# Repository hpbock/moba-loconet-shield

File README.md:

# LocoNet Shield (February 2026 Version)

Copyright (c) 2026 Dr.-Ing. Hans-Peter Bock <ln-shield@avaapgh.de>

# License & Legal Notices

This hardware design (schematic and board layout) is a modified version (derivative work) of the "LocoShield" project by John Plocher (SPCoast Electronics).

Based on the conditions of the original license, this derivative work is licensed under the CERN Open Hardware Licence v1.2 (CERN OHL v1.2).

- The unmodified original schematic originates from the repository: <https://github.com/plocher/LocoShield>
- The full license text of the CERN OHL v1.2 is included in the [LICENSE.txt](LICENSE.txt) file within this repository.
- The source files for this modified design are permanently available at: <https://github.com/hpbock/moba-loconet-shield>

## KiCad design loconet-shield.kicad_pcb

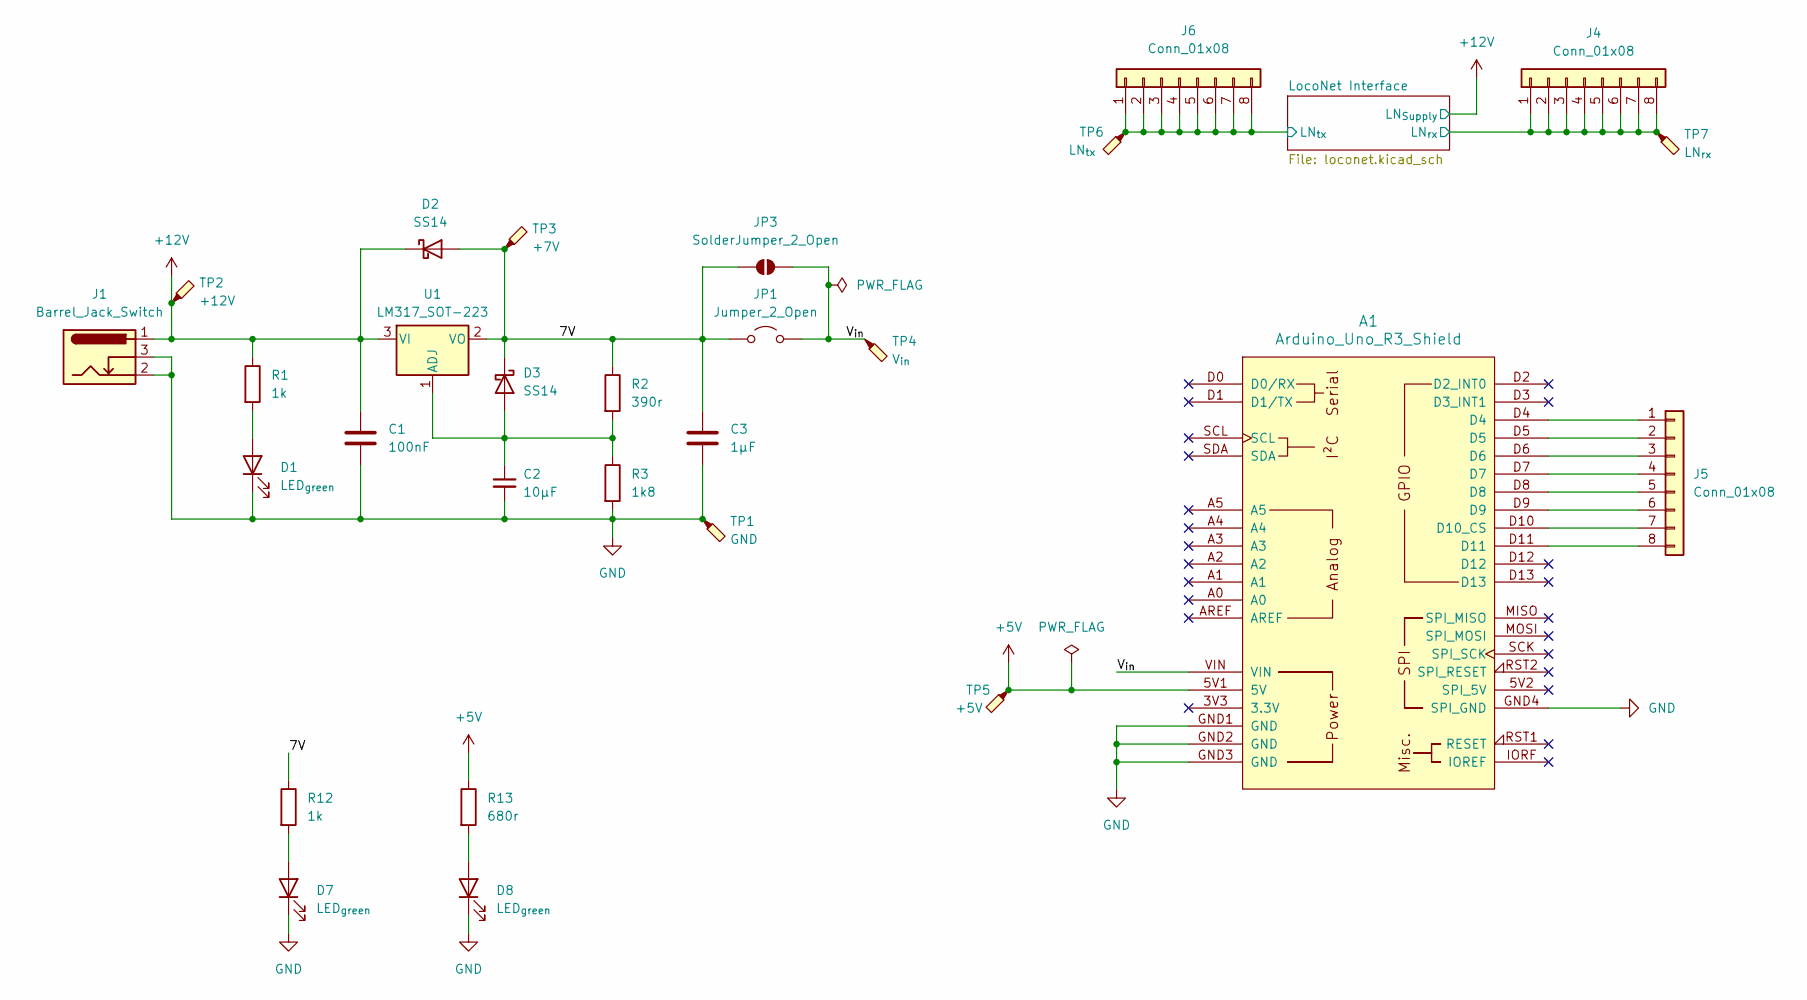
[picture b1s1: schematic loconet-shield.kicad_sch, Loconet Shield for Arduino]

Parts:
A1: Arduino_Uno_R3_Shield
C1: 100nF; C_0603_1608Metric; LCSC C14663
C2: 10µF; C_0603_1608Metric; LCSC C19702
C3: 1µF; C_0603_1608Metric; LCSC C15849
D1, D7, D8: LED_{green}; LED_0603_1608Metric; LCSC C7496812
D2, D3: SS14; D_SMA; LCSC C2480
J1: Barrel_Jack_Switch; BarrelJack_CLIFF_FC681465S_SMT_Horizontal
J4, J5, J6: Conn_01x08; PinHeader_1x08_P2.54mm_Vertical
JP1: Jumper_2_Open; PinHeader_1x02_P2.54mm_Vertical
JP3: SolderJumper_2_Open; SolderJumper-2_P1.3mm_Open_TrianglePad1.0x1.5mm
R1, R12: 1k; R_0603_1608Metric; LCSC C21190
R2: 390r; R_0603_1608Metric; LCSC C23151
R3: 1k8; R_0603_1608Metric; LCSC C4177
R13: 680r; R_0603_1608Metric; LCSC C23228
TP1: GND; TestPoint_Pad_2.0x2.0mm
TP2: +12V; TestPoint_Pad_D2.0mm
TP3: +7V; TestPoint_Pad_D2.0mm
TP4: V_{in}; TestPoint_Pad_D2.0mm
TP5: +5V; TestPoint_Pad_D2.0mm
TP6: LN_{tx}; TestPoint_Pad_D2.0mm
TP7: LN_{rx}; TestPoint_Pad_D2.0mm
U1: LM317_SOT-223; SOT-223-3_TabPin2; LCSC C5296732

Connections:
+5V: A1.5V1 (5V), R13.1, TP5.1; also elsewhere on the board
+12V: C1.1, D2.1 (K), J1.1, R1.1, TP2.1, U1.3 (VI); also elsewhere on the board
/7V: C3.1, D2.2 (A), D3.1 (K), JP1.1 (A), JP3.1 (A), R2.1, R12.1, TP3.1, U1.2 (VO)
/LocoNet Interface/LN_{rx}: J4.1, J4.2, J4.3, J4.4, J4.5, J4.6, J4.7, J4.8, TP7.1; also elsewhere on the board
/LocoNet Interface/LN_{tx}: J6.1, J6.2, J6.3, J6.4, J6.5, J6.6, J6.7, J6.8, TP6.1; also elsewhere on the board
/V_{in}: A1.VIN, JP1.2 (B), JP3.2 (B), TP4.1
GND: A1.GND1 (GND), A1.GND2 (GND), A1.GND3 (GND), A1.GND4 (SPI_GND), C1.2, C2.2, C3.2, D1.1 (K), D7.1 (K), D8.1 (K), J1.2, J1.3, R3.2, TP1.1; also elsewhere on the board
unnamed: A1.D10 (D10_CS), J5.7
unnamed: D1.2 (A), R1.2
unnamed: C2.1, D3.2 (A), R2.2, R3.1, U1.1 (ADJ)
unnamed: D7.2 (A), R12.2
unnamed: D8.2 (A), R13.2
unnamed: A1.D4, J5.1
unnamed: A1.D5, J5.2
unnamed: A1.D6, J5.3
unnamed: A1.D7, J5.4
unnamed: A1.D8, J5.5
unnamed: A1.D9, J5.6
unnamed: A1.D11, J5.8

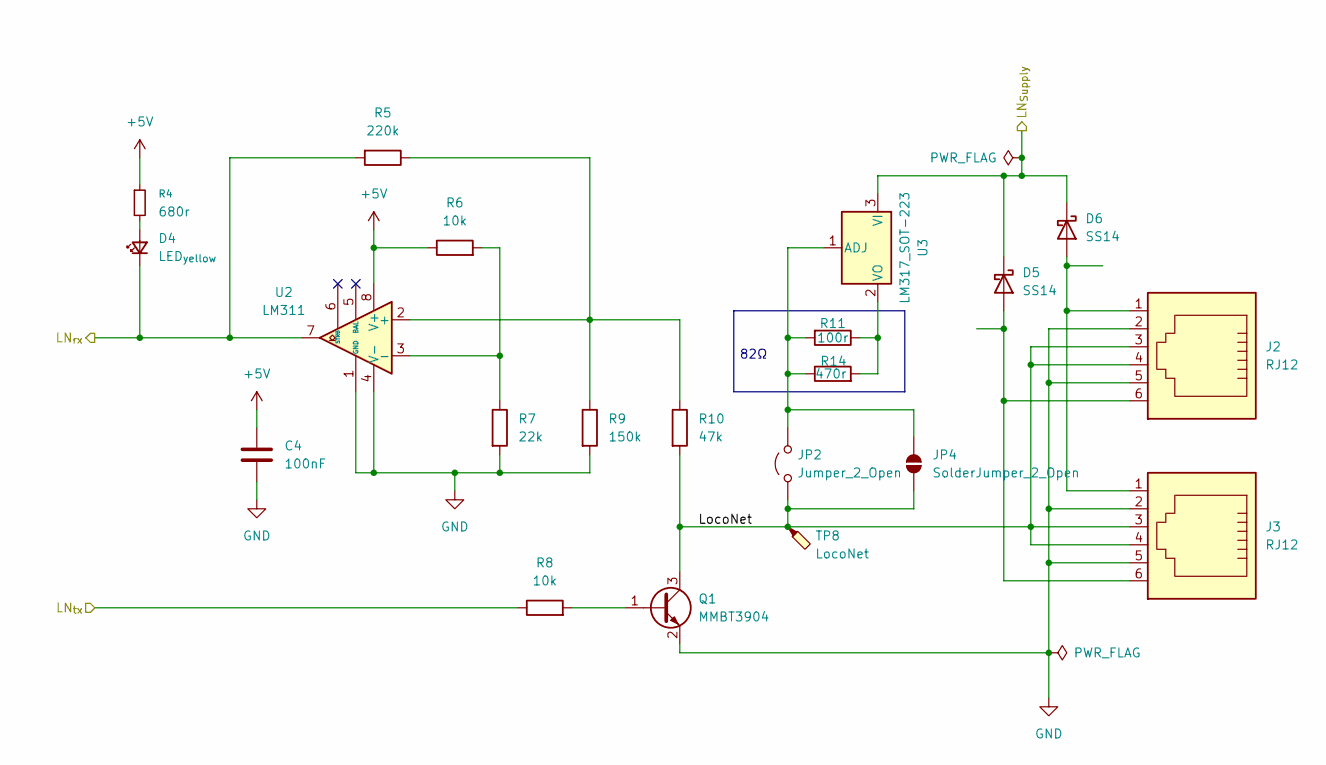
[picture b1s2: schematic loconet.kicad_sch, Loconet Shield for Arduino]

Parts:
C4: 100nF; C_0603_1608Metric; LCSC C14663
D4: LED_{yellow}; LED_0603_1608Metric; LCSC C7496811
D5, D6: SS14; D_SMA; LCSC C2480
J2, J3: RJ12; RJ12_Amphenol_54601-x06_Horizontal
JP2: Jumper_2_Open; PinHeader_1x02_P2.54mm_Vertical
JP4: SolderJumper_2_Open; SolderJumper-2_P1.3mm_Open_TrianglePad1.0x1.5mm
Q1: MMBT3904; SOT-23; LCSC C20526
R4: 680r; R_0603_1608Metric; LCSC C23228
R5: 220k; R_0603_1608Metric; LCSC C22961
R6, R8: 10k; R_0603_1608Metric; LCSC C25804
R7: 22k; R_0603_1608Metric; LCSC C31850
R9: 150k; R_0603_1608Metric; LCSC C22807
R10: 47k; R_0603_1608Metric; LCSC C25819
R11: 100r; R_0603_1608Metric; LCSC C22775
R14: 470r; R_0603_1608Metric; LCSC C23179
TP8: LocoNet; TestPoint_Pad_D2.0mm
U2: LM311; SO-8_3.9x4.9mm_P1.27mm; LCSC C12597
U3: LM317_SOT-223; SOT-223-3_TabPin2; LCSC C5296732

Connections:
+5V: C4.1, R4.1, R6.1, U2.8 (V+); also elsewhere on the board
+12V: D5.1 (K), D6.1 (K), U3.3 (VI); also elsewhere on the board
/LocoNet Interface/LN_{rx}: D4.1 (K), R5.2, U2.7; also elsewhere on the board
/LocoNet Interface/LN_{tx}: R8.1; also elsewhere on the board
/LocoNet Interface/LocoNet: J2.3, J2.4, J3.3, J3.4, JP2.1 (A), JP4.2 (B), Q1.3 (C), R10.2, TP8.1
GND: C4.2, J2.2, J2.5, J3.2, J3.5, Q1.2 (E), R7.2, R9.2, U2.1 (GND), U2.4 (V-); also elsewhere on the board
unnamed: D4.2 (A), R4.2
unnamed: D5.2 (A), J2.6, J3.6
unnamed: D6.2 (A), J2.1, J3.1
unnamed: JP2.2 (B), JP4.1 (A), R11.2, R14.1, U3.1 (ADJ)
unnamed: Q1.1 (B), R8.2
unnamed: R5.1, R9.1, R10.1, U2.2 (+)
unnamed: R6.2, R7.1, U2.3 (-)
unnamed: R11.1, R14.2, U3.2 (VO)

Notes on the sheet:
82Ω

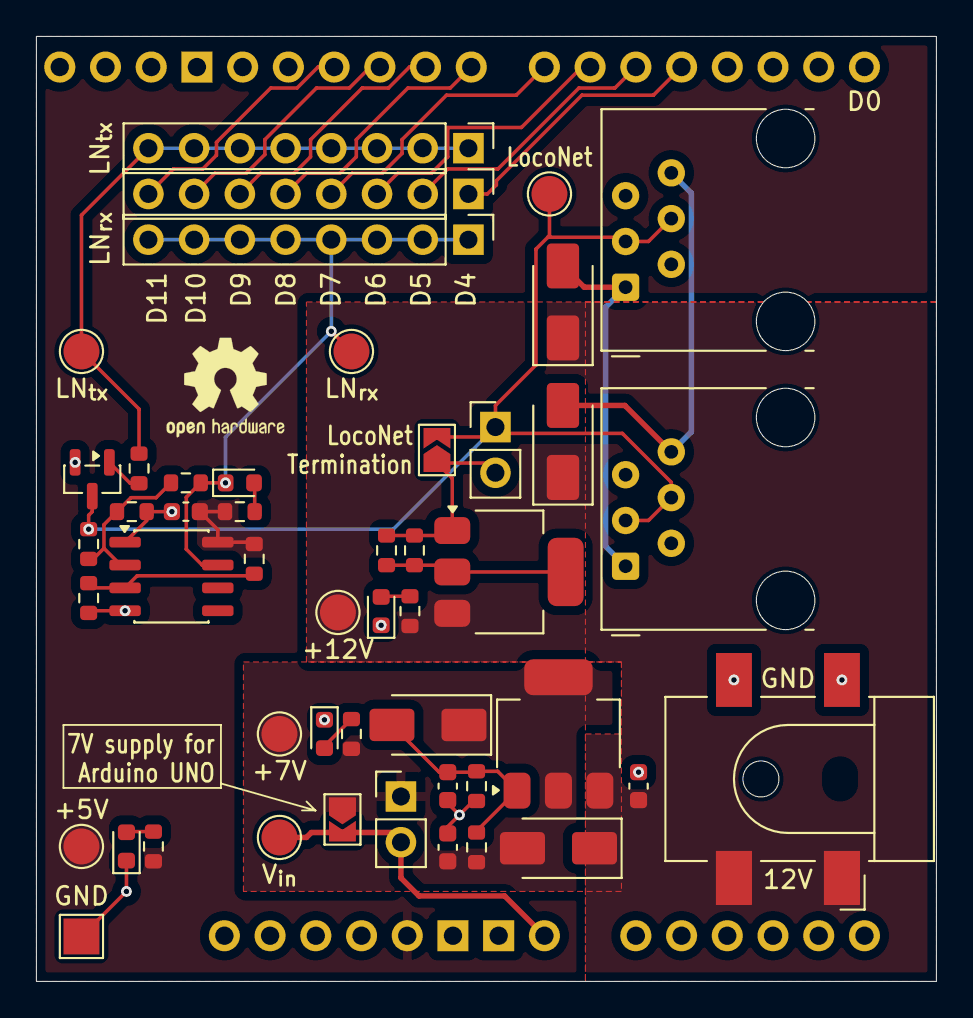
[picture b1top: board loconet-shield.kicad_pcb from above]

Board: 2 copper layers, 50.0 x 52.5 mm, 49 parts (0 on the bottom side), 28 nets.

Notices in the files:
loconet-shield.kicad_pcb:
Licensed under CERN OHL v1.2.
